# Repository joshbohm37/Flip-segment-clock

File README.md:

# Flip Segment Clock
A desktop clock centered around electromechanical 7 segment flip displays.

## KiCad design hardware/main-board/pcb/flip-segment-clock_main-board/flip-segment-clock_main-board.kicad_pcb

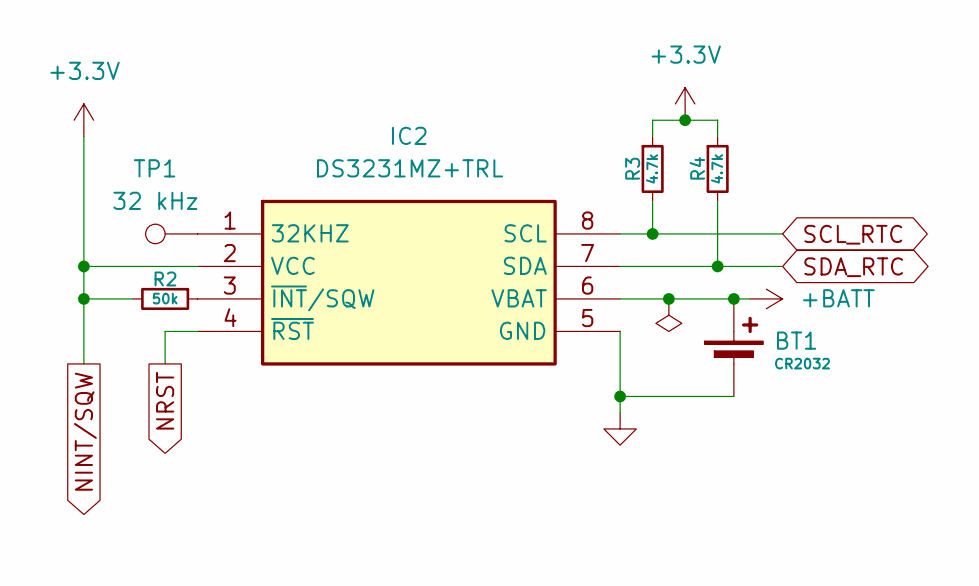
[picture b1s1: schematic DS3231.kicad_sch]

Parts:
BT1: CR2032; BatteryHolder_Keystone_1057_1x2032
IC2: DS3231MZ+TRL; SOIC127P600X175-8N; Mouser Part Number 700-DS3231MZ+TRL
R2: 50k; R_0402_1005Metric
R3, R4: 4.7k; R_0402_1005Metric
TP1: 32 kHz; TestPoint_Pad_D2.5mm

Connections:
+BATT: BT1.1 (+), IC2.6 (VBAT); also elsewhere on the board
GND: BT1.2 (-), IC2.5 (GND); also elsewhere on the board
NINT/SQW: IC2.2 (VCC), R2.2, R3.1, R4.1; also elsewhere on the board
NRST: IC2.4 (~RST)
unnamed: IC2.1 (32KHZ), TP1.1
unnamed: IC2.3 (~INT/SQW), R2.1
SCL_RTC: IC2.8 (SCL), R3.2
SDA_RTC: IC2.7 (SDA), R4.2

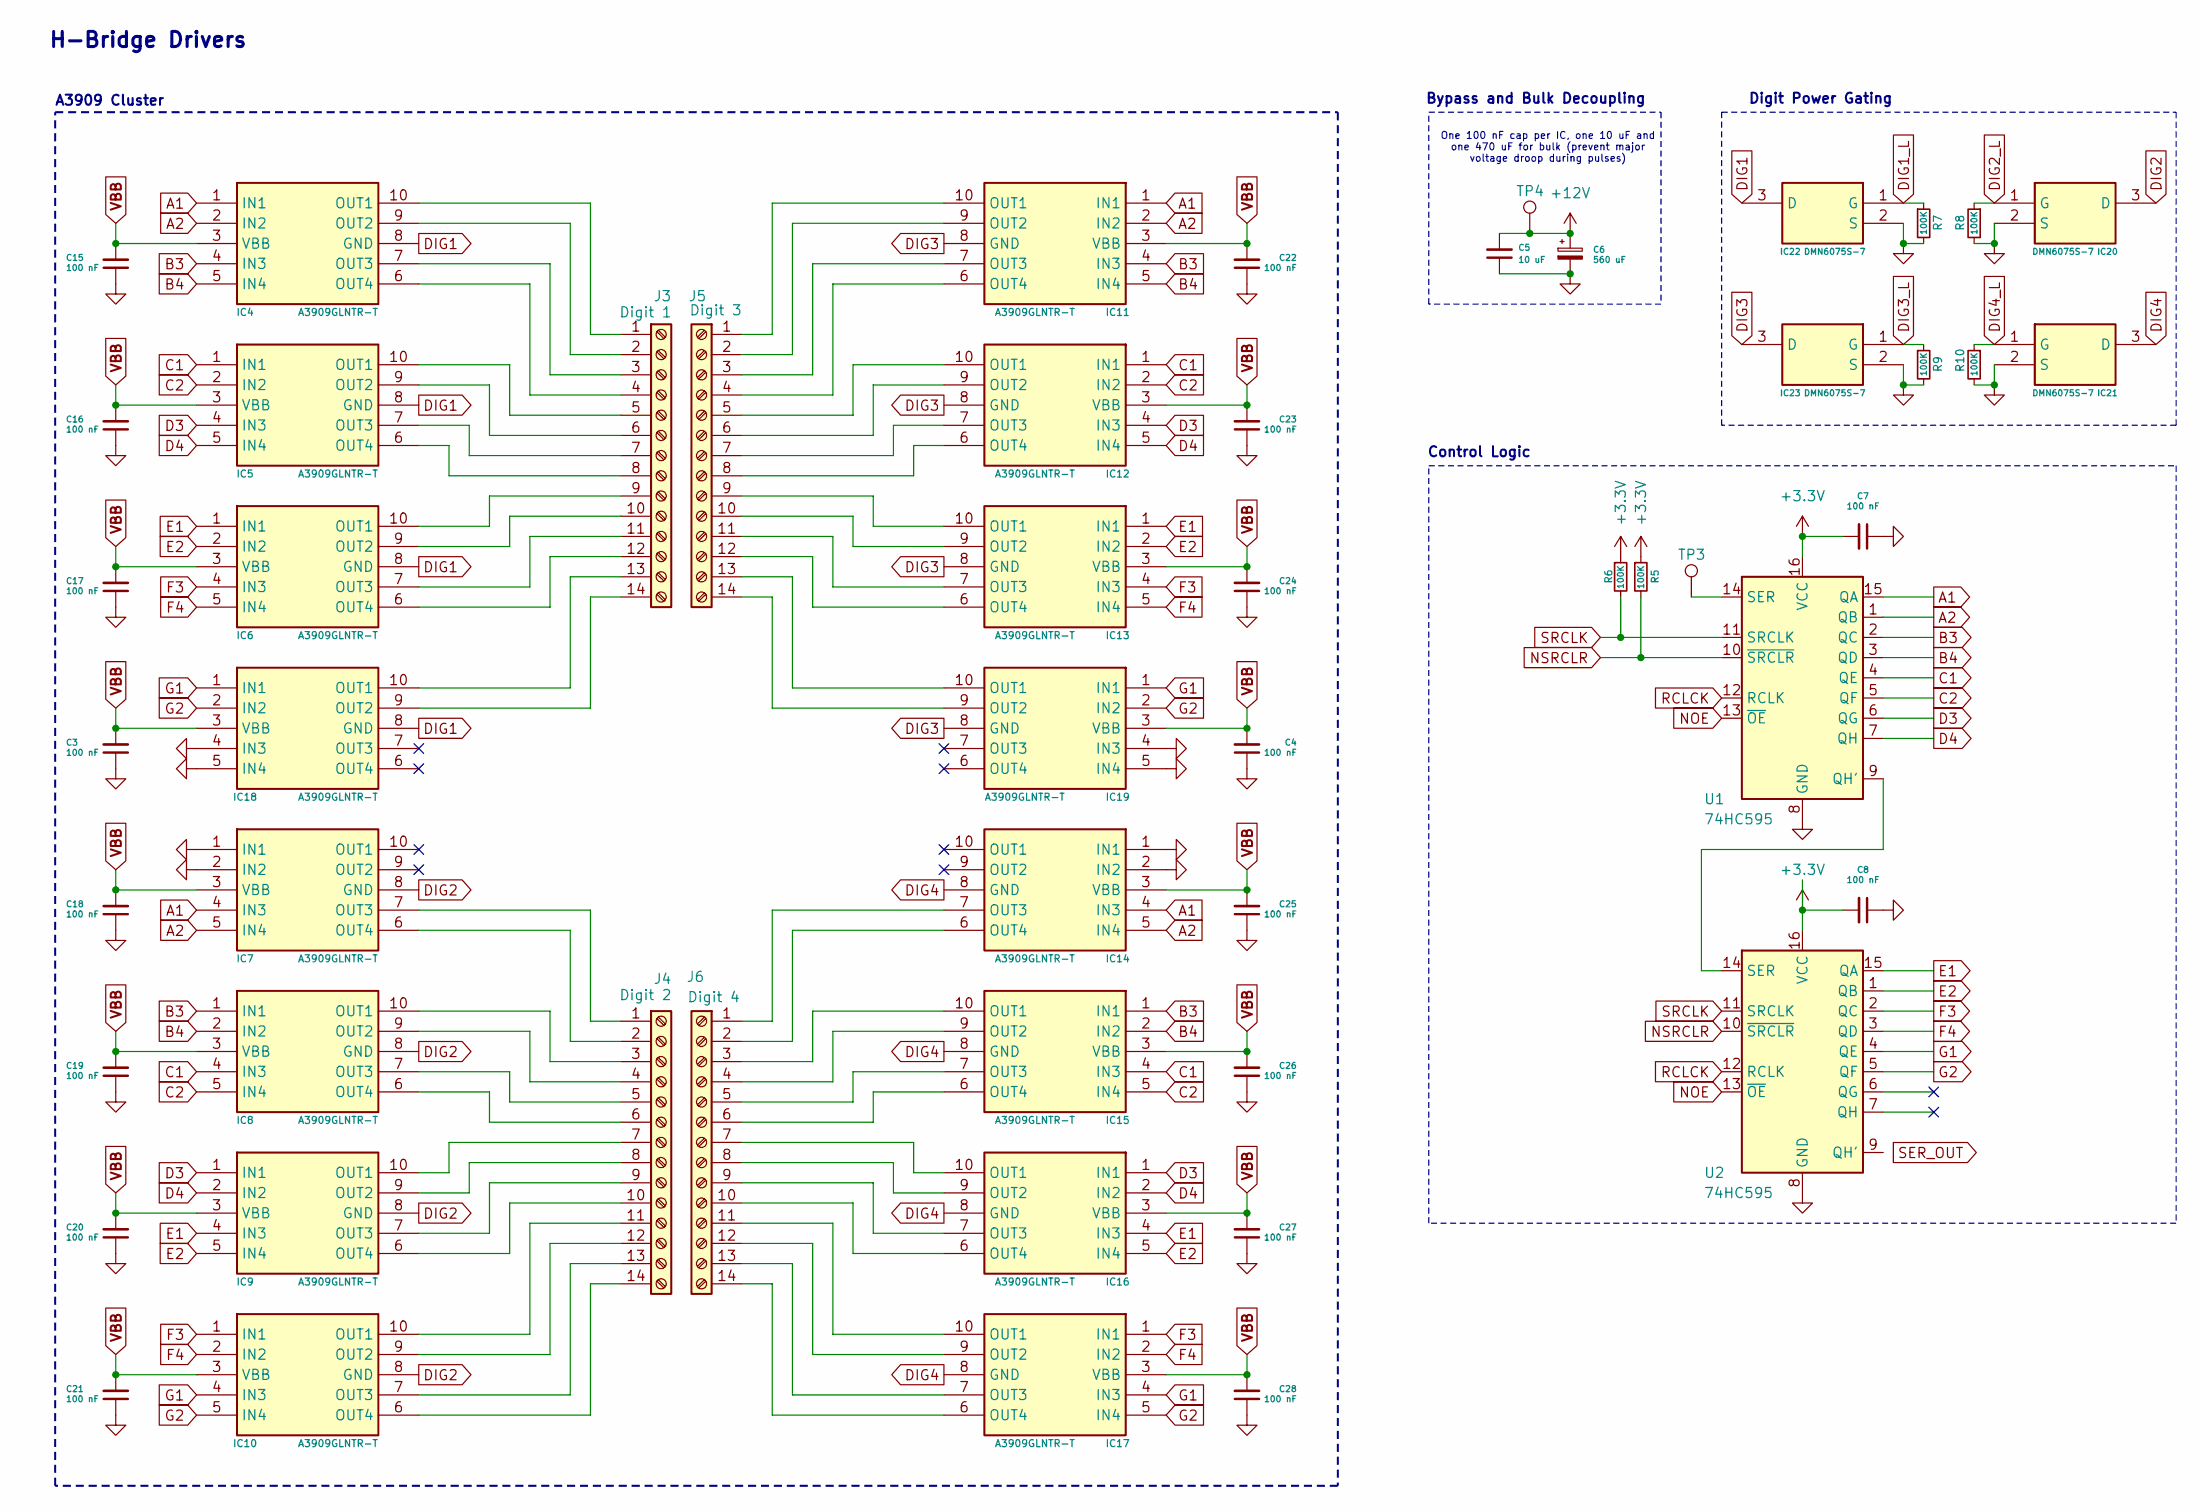
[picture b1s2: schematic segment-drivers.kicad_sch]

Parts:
C3, C4, C7, C8, C15, C16, C17, C18, C19, C20, C21, C22, C23, C24, C25, C26, C27, C28: 100 nF; C_0402_1005Metric; Manufacturer part # CL05B104KA5NNNC; LCSC C155422
C5: 10 uF; C_1206_3216Metric; Manufacturer part # CL31A106KAHNNNE; LCSC C9807
C6: 560 uF; C_Elec_10x10.2; Manufacturer part # EMZR350ARA561MJA0G; LCSC C2163314
IC4, IC5, IC6, IC7, IC8, IC9, IC10, IC11, IC12, IC13, IC14, IC15, IC16, IC17, IC18, IC19: A3909GLNTR-T; SOP100P600X175-10N; Mouser Part Number 250-A3909GLNTR-T
IC20, IC21, IC22, IC23: DMN6075S-7; SOT96P240X110-3N; Mouser Part Number 621-DMN6075S-7
J3: Digit 1; TerminalBlock_Xinya_XY308-2.54-14P_1x14_P2.54mm_Horizontal
J4: Digit 2; TerminalBlock_Xinya_XY308-2.54-14P_1x14_P2.54mm_Horizontal
J5: Digit 3; TerminalBlock_Xinya_XY308-2.54-14P_1x14_P2.54mm_Horizontal
J6: Digit 4; TerminalBlock_Xinya_XY308-2.54-14P_1x14_P2.54mm_Horizontal
R5, R6: 100K; R_0402_1005Metric; Manufacturer part # 0402WGF1003TCE; LCSC C25741
R7, R8, R9, R10: 100K; R_0402_1005Metric
TP3: SER; TestPoint_Pad_D1.5mm
TP4: 12v; TestPoint_Pad_D1.5mm
U1, U2: 74HC595; SOIC-16_3.9x9.9mm_P1.27mm; Manufacturer part # 74HC595D,118; LCSC C5947

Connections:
+12V: C5.2, C6.1, TP4.1; also elsewhere on the board
A1: IC4.1 (IN1), IC7.4 (IN3), IC11.1 (IN1), IC14.4 (IN3), U1.15 (QA)
A2: IC4.2 (IN2), IC7.5 (IN4), IC11.2 (IN2), IC14.5 (IN4), U1.1 (QB)
B3: IC4.4 (IN3), IC8.1 (IN1), IC11.4 (IN3), IC15.1 (IN1), U1.2 (QC)
B4: IC4.5 (IN4), IC8.2 (IN2), IC11.5 (IN4), IC15.2 (IN2), U1.3 (QD)
C1: IC5.1 (IN1), IC8.4 (IN3), IC12.1 (IN1), IC15.4 (IN3), U1.4 (QE)
C2: IC5.2 (IN2), IC8.5 (IN4), IC12.2 (IN2), IC15.5 (IN4), U1.5 (QF)
D3: IC5.4 (IN3), IC9.1 (IN1), IC12.4 (IN3), IC16.1 (IN1), U1.6 (QG)
D4: IC5.5 (IN4), IC9.2 (IN2), IC12.5 (IN4), IC16.2 (IN2), U1.7 (QH)
DIG1: IC4.8 (GND), IC5.8 (GND), IC6.8 (GND), IC18.8 (GND), IC22.3 (D)
DIG1_L: IC22.1 (G), R7.1
DIG2: IC7.8 (GND), IC8.8 (GND), IC9.8 (GND), IC10.8 (GND), IC20.3 (D)
DIG2_L: IC20.1 (G), R8.1
DIG3: IC11.8 (GND), IC12.8 (GND), IC13.8 (GND), IC19.8 (GND), IC23.3 (D)
DIG3_L: IC23.1 (G), R9.1
DIG4: IC14.8 (GND), IC15.8 (GND), IC16.8 (GND), IC17.8 (GND), IC21.3 (D)
DIG4_L: IC21.1 (G), R10.1
E1: IC6.1 (IN1), IC9.4 (IN3), IC13.1 (IN1), IC16.4 (IN3), U2.15 (QA)
E2: IC6.2 (IN2), IC9.5 (IN4), IC13.2 (IN2), IC16.5 (IN4), U2.1 (QB)
F3: IC6.4 (IN3), IC10.1 (IN1), IC13.4 (IN3), IC17.1 (IN1), U2.2 (QC)
F4: IC6.5 (IN4), IC10.2 (IN2), IC13.5 (IN4), IC17.2 (IN2), U2.3 (QD)
G1: IC10.4 (IN3), IC17.4 (IN3), IC18.1 (IN1), IC19.1 (IN1), U2.4 (QE)
G2: IC10.5 (IN4), IC17.5 (IN4), IC18.2 (IN2), IC19.2 (IN2), U2.5 (QF)
GND: C3.1, C4.1, C5.1, C6.2, C7.1, C8.1, C15.1, C16.1, C17.1, C18.1, C19.1, C20.1, C21.1, C22.1, C23.1, C24.1, C25.1, C26.1, C27.1, C28.1, IC7.1 (IN1), IC7.2 (IN2), IC14.1 (IN1), IC14.2 (IN2), IC18.4 (IN3), IC18.5 (IN4), IC19.4 (IN3), IC19.5 (IN4), IC20.2 (S), IC21.2 (S), IC22.2 (S), IC23.2 (S), R7.2, R8.2, R9.2, R10.2, U1.8 (GND), U2.8 (GND); also elsewhere on the board
NINT/SQW: C7.2, C8.2, R5.1, R6.1, U1.16 (VCC), U2.16 (VCC); also elsewhere on the board
NOE: U1.13 (~OE), U2.13 (~OE)
NSRCLR: R5.2, U1.10 (~SRCLR), U2.10 (~SRCLR)
unnamed: IC4.10 (OUT1), J3.1
unnamed: IC4.9 (OUT2), J3.2
unnamed: IC4.7 (OUT3), J3.3
unnamed: IC4.6 (OUT4), J3.4
unnamed: IC5.10 (OUT1), J3.5
unnamed: IC5.9 (OUT2), J3.6
unnamed: IC5.7 (OUT3), J3.7
unnamed: IC5.6 (OUT4), J3.8
unnamed: IC6.10 (OUT1), J3.9
unnamed: IC6.9 (OUT2), J3.10
unnamed: IC6.7 (OUT3), J3.11
unnamed: IC6.6 (OUT4), J3.12
unnamed: IC7.7 (OUT3), J4.1
unnamed: IC7.6 (OUT4), J4.2
unnamed: IC8.10 (OUT1), J4.3
unnamed: IC8.9 (OUT2), J4.4
unnamed: IC8.7 (OUT3), J4.5
unnamed: IC8.6 (OUT4), J4.6
unnamed: IC9.10 (OUT1), J4.7
unnamed: IC9.9 (OUT2), J4.8
unnamed: IC9.7 (OUT3), J4.9
unnamed: IC9.6 (OUT4), J4.10
unnamed: IC10.10 (OUT1), J4.11
unnamed: IC10.9 (OUT2), J4.12
unnamed: IC10.7 (OUT3), J4.13
unnamed: IC10.6 (OUT4), J4.14
unnamed: IC11.10 (OUT1), J5.1
unnamed: IC11.9 (OUT2), J5.2
unnamed: IC11.7 (OUT3), J5.3
unnamed: IC11.6 (OUT4), J5.4
unnamed: IC12.10 (OUT1), J5.5
unnamed: IC12.9 (OUT2), J5.6
unnamed: IC12.7 (OUT3), J5.7
unnamed: IC12.6 (OUT4), J5.8
unnamed: IC13.10 (OUT1), J5.9
unnamed: IC13.9 (OUT2), J5.10
unnamed: IC13.7 (OUT3), J5.11
unnamed: IC13.6 (OUT4), J5.12
unnamed: IC14.7 (OUT3), J6.1
unnamed: IC14.6 (OUT4), J6.2
unnamed: IC15.10 (OUT1), J6.3
unnamed: IC15.9 (OUT2), J6.4
unnamed: IC15.7 (OUT3), J6.5
unnamed: IC15.6 (OUT4), J6.6
unnamed: IC16.10 (OUT1), J6.7
unnamed: IC16.9 (OUT2), J6.8
unnamed: IC16.7 (OUT3), J6.9
unnamed: IC16.6 (OUT4), J6.10
unnamed: IC17.10 (OUT1), J6.11
unnamed: IC17.9 (OUT2), J6.12
unnamed: IC17.7 (OUT3), J6.13
unnamed: IC17.6 (OUT4), J6.14
unnamed: IC18.10 (OUT1), J3.13
unnamed: IC18.9 (OUT2), J3.14
unnamed: IC19.10 (OUT1), J5.13
unnamed: IC19.9 (OUT2), J5.14
unnamed: U1.9 (QH'), U2.14 (SER)
unnamed: TP3.1, U1.14 (SER)
RCLCK: U1.12 (RCLK), U2.12 (RCLK)
SRCLK: R6.2, U1.11 (SRCLK), U2.11 (SRCLK)
VBB: C3.2, C4.2, C15.2, C16.2, C17.2, C18.2, C19.2, C20.2, C21.2, C22.2, C23.2, C24.2, C25.2, C26.2, C27.2, C28.2, IC4.3 (VBB), IC5.3 (VBB), IC6.3 (VBB), IC7.3 (VBB), IC8.3 (VBB), IC9.3 (VBB), IC10.3 (VBB), IC11.3 (VBB), IC12.3 (VBB), IC13.3 (VBB), IC14.3 (VBB), IC15.3 (VBB), IC16.3 (VBB), IC17.3 (VBB), IC18.3 (VBB), IC19.3 (VBB)

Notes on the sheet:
Control Logic
H-Bridge Drivers
Digit Power Gating
Bypass and Bulk Decoupling
One 100 nF cap per IC, one 10 uF and one 470 uF for bulk (prevent major voltage droop during pulses)
A3909 Cluster

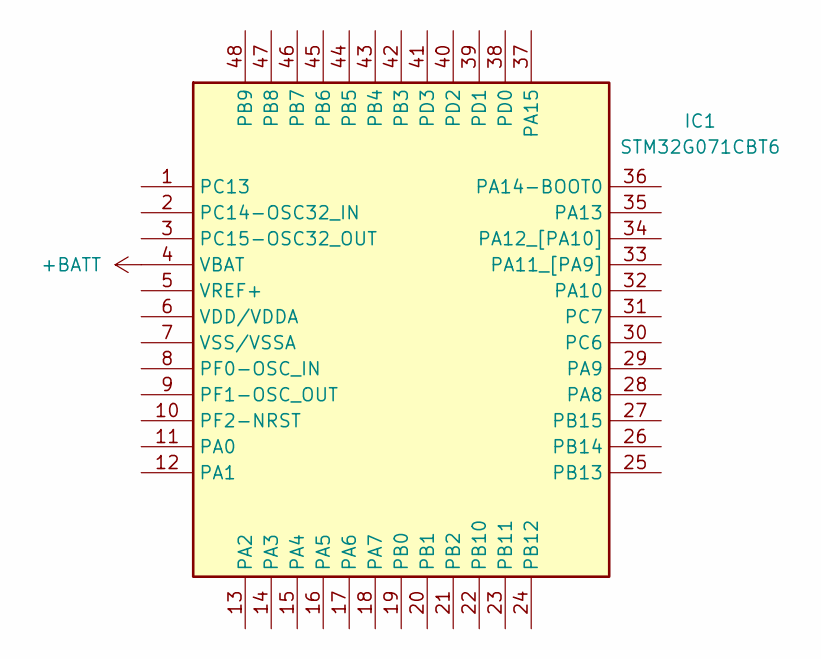
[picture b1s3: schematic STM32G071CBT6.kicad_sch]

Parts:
IC1: STM32G071CBT6; QFP50P900X900X160-48N; Mouser Part Number 511-STM32G071CBT6

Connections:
+BATT: IC1.4 (VBAT); also elsewhere on the board

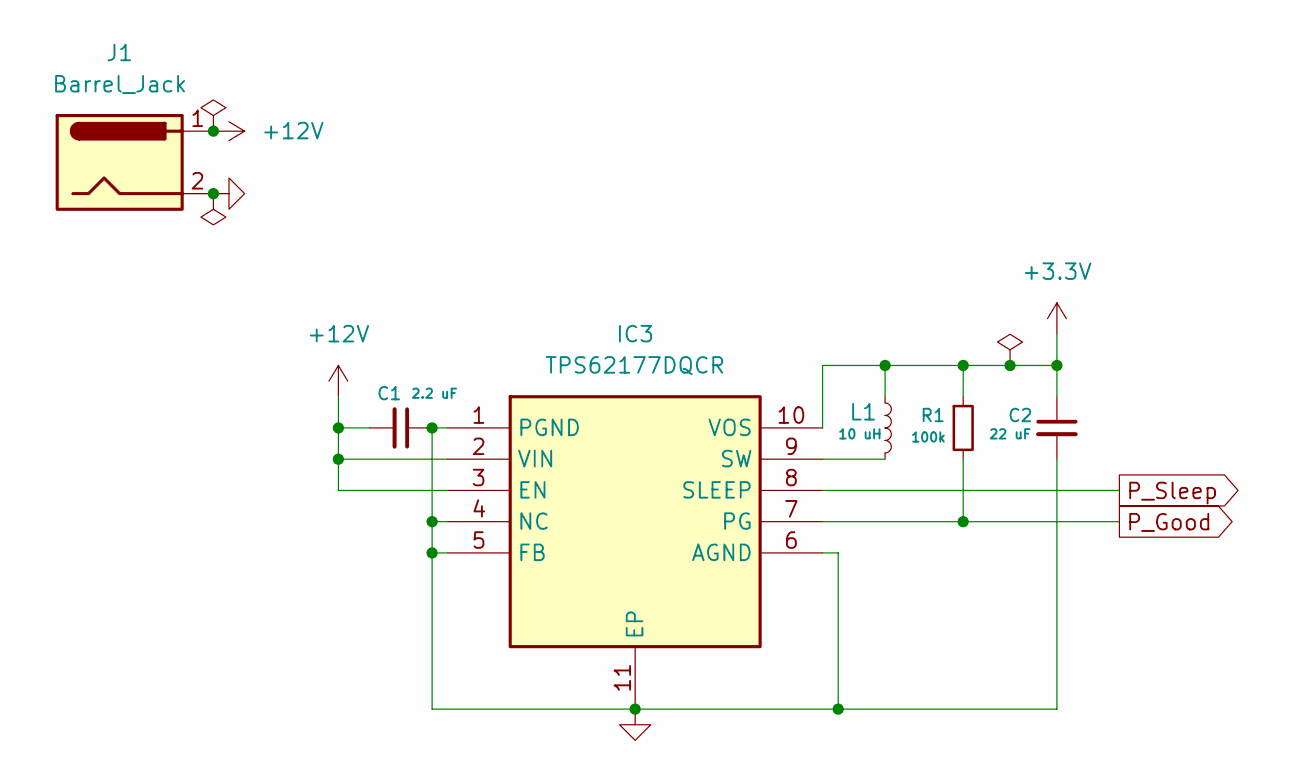
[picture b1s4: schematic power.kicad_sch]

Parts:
C1: 2.2 uF; C_0402_1005Metric
C2: 22 uF; C_0402_1005Metric
IC3: TPS62177DQCR; SON50P200X300X80-11N; Mouser Part Number 595-TPS62177DQCR
J1: Barrel_Jack; BarrelJack_SwitchcraftConxall_RAPC10U_Horizontal
L1: 10 uH; L_Coilcraft_LPS4018
R1: 100k; R_0402_1005Metric

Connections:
+12V: C1.2, IC3.2 (VIN), IC3.3 (EN), J1.1; also elsewhere on the board
GND: C1.1, C2.2, IC3.1 (PGND), IC3.4 (NC), IC3.5 (FB), IC3.6 (AGND), IC3.11 (EP), J1.2; also elsewhere on the board
NINT/SQW: C2.1, IC3.10 (VOS), L1.1, R1.1; also elsewhere on the board
unnamed: IC3.9 (SW), L1.2
P_Good: IC3.7 (PG), R1.2
P_Sleep: IC3.8 (SLEEP)

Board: 2 copper layers, 67 parts (0 on the bottom side), 95 nets, no tracks yet.

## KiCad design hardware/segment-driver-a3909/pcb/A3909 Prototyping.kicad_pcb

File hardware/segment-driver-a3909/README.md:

# a3909 segment driver breakout board
A breakout board used for driving 1 inch 7 segment electromechanical displays. Built around the A3909. Designed to test electrical properties/control mechanisms for the alfazeta 7 segment flip displays. Design will be integrated into final main board.

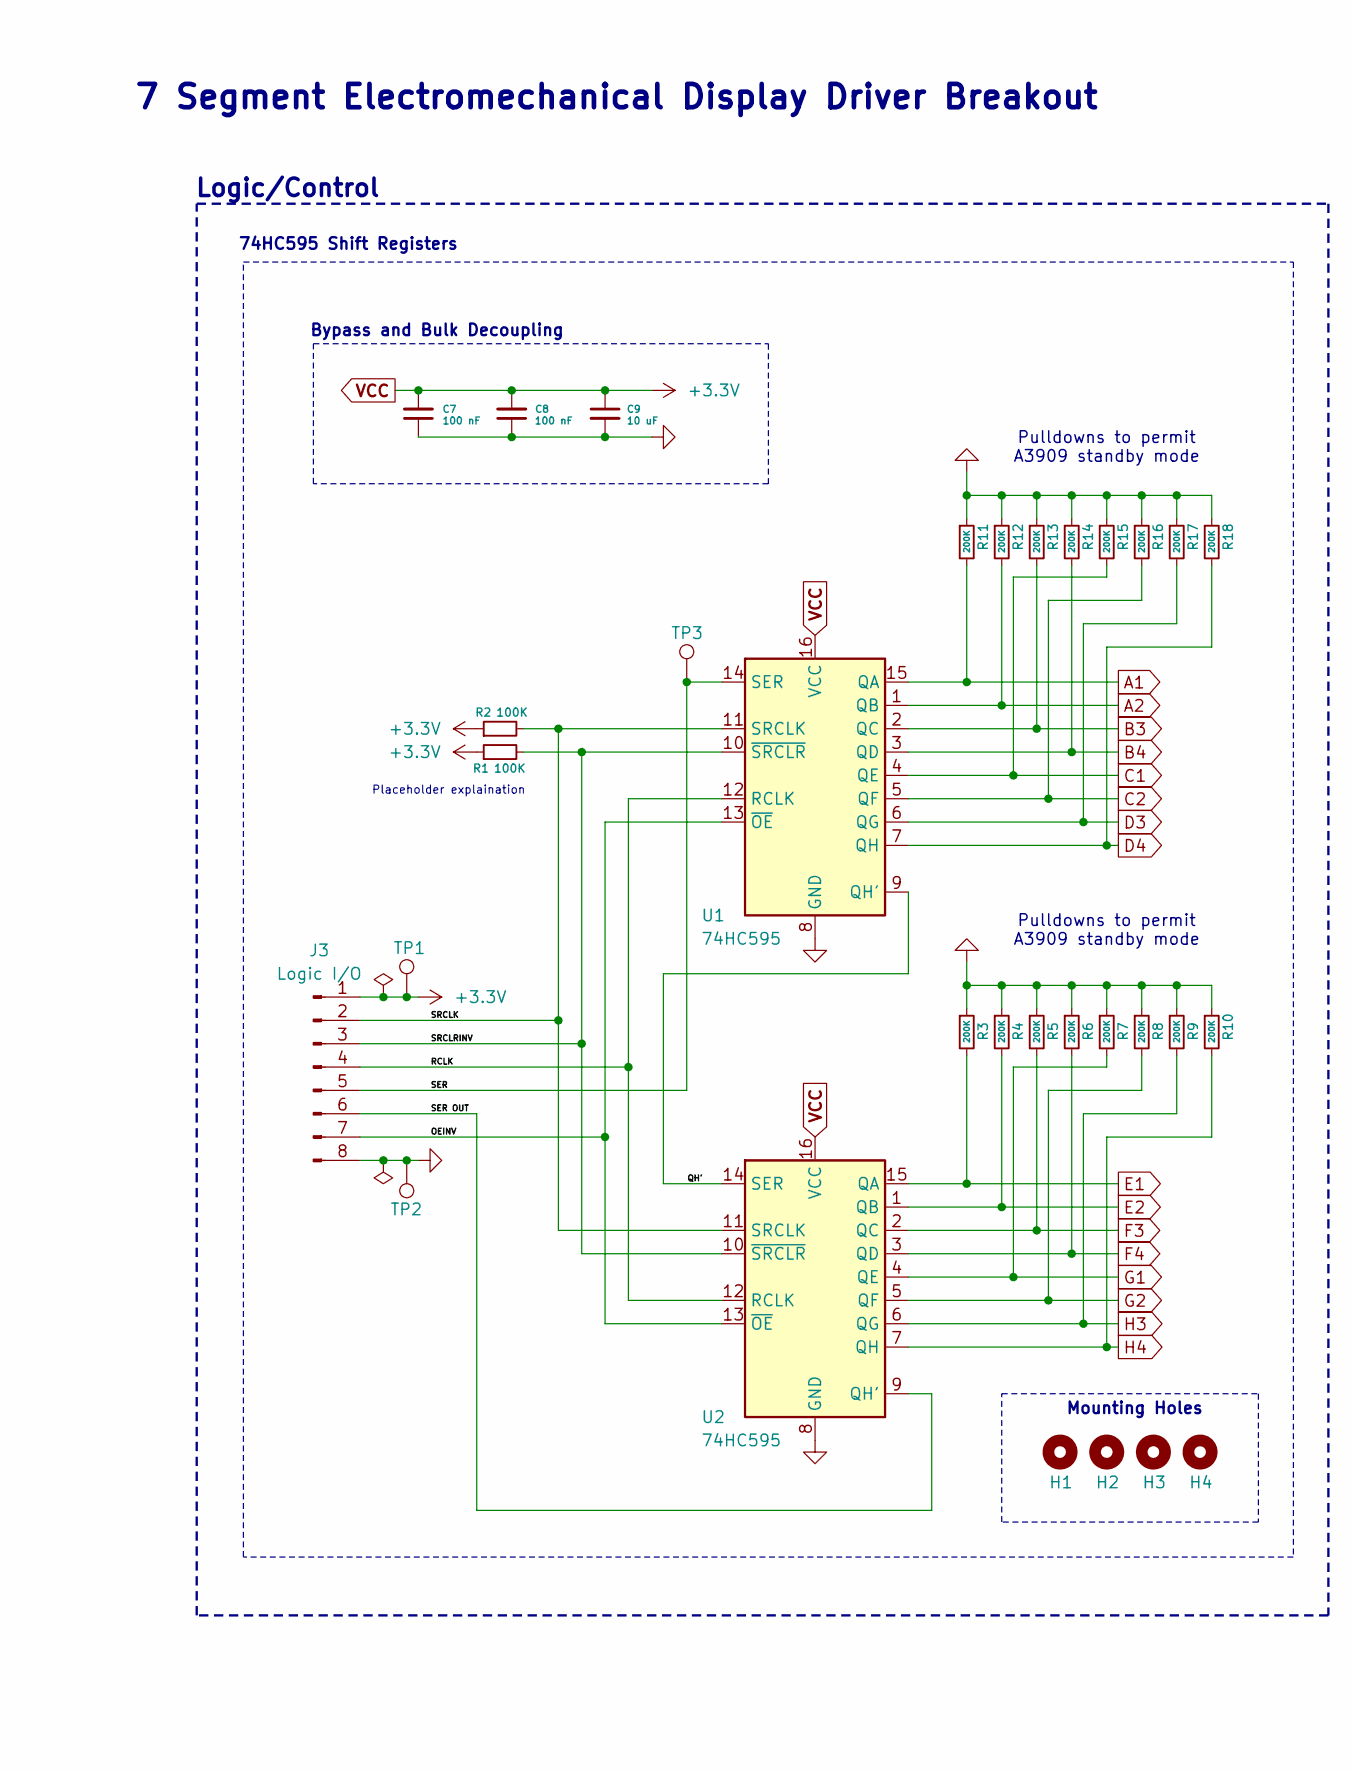
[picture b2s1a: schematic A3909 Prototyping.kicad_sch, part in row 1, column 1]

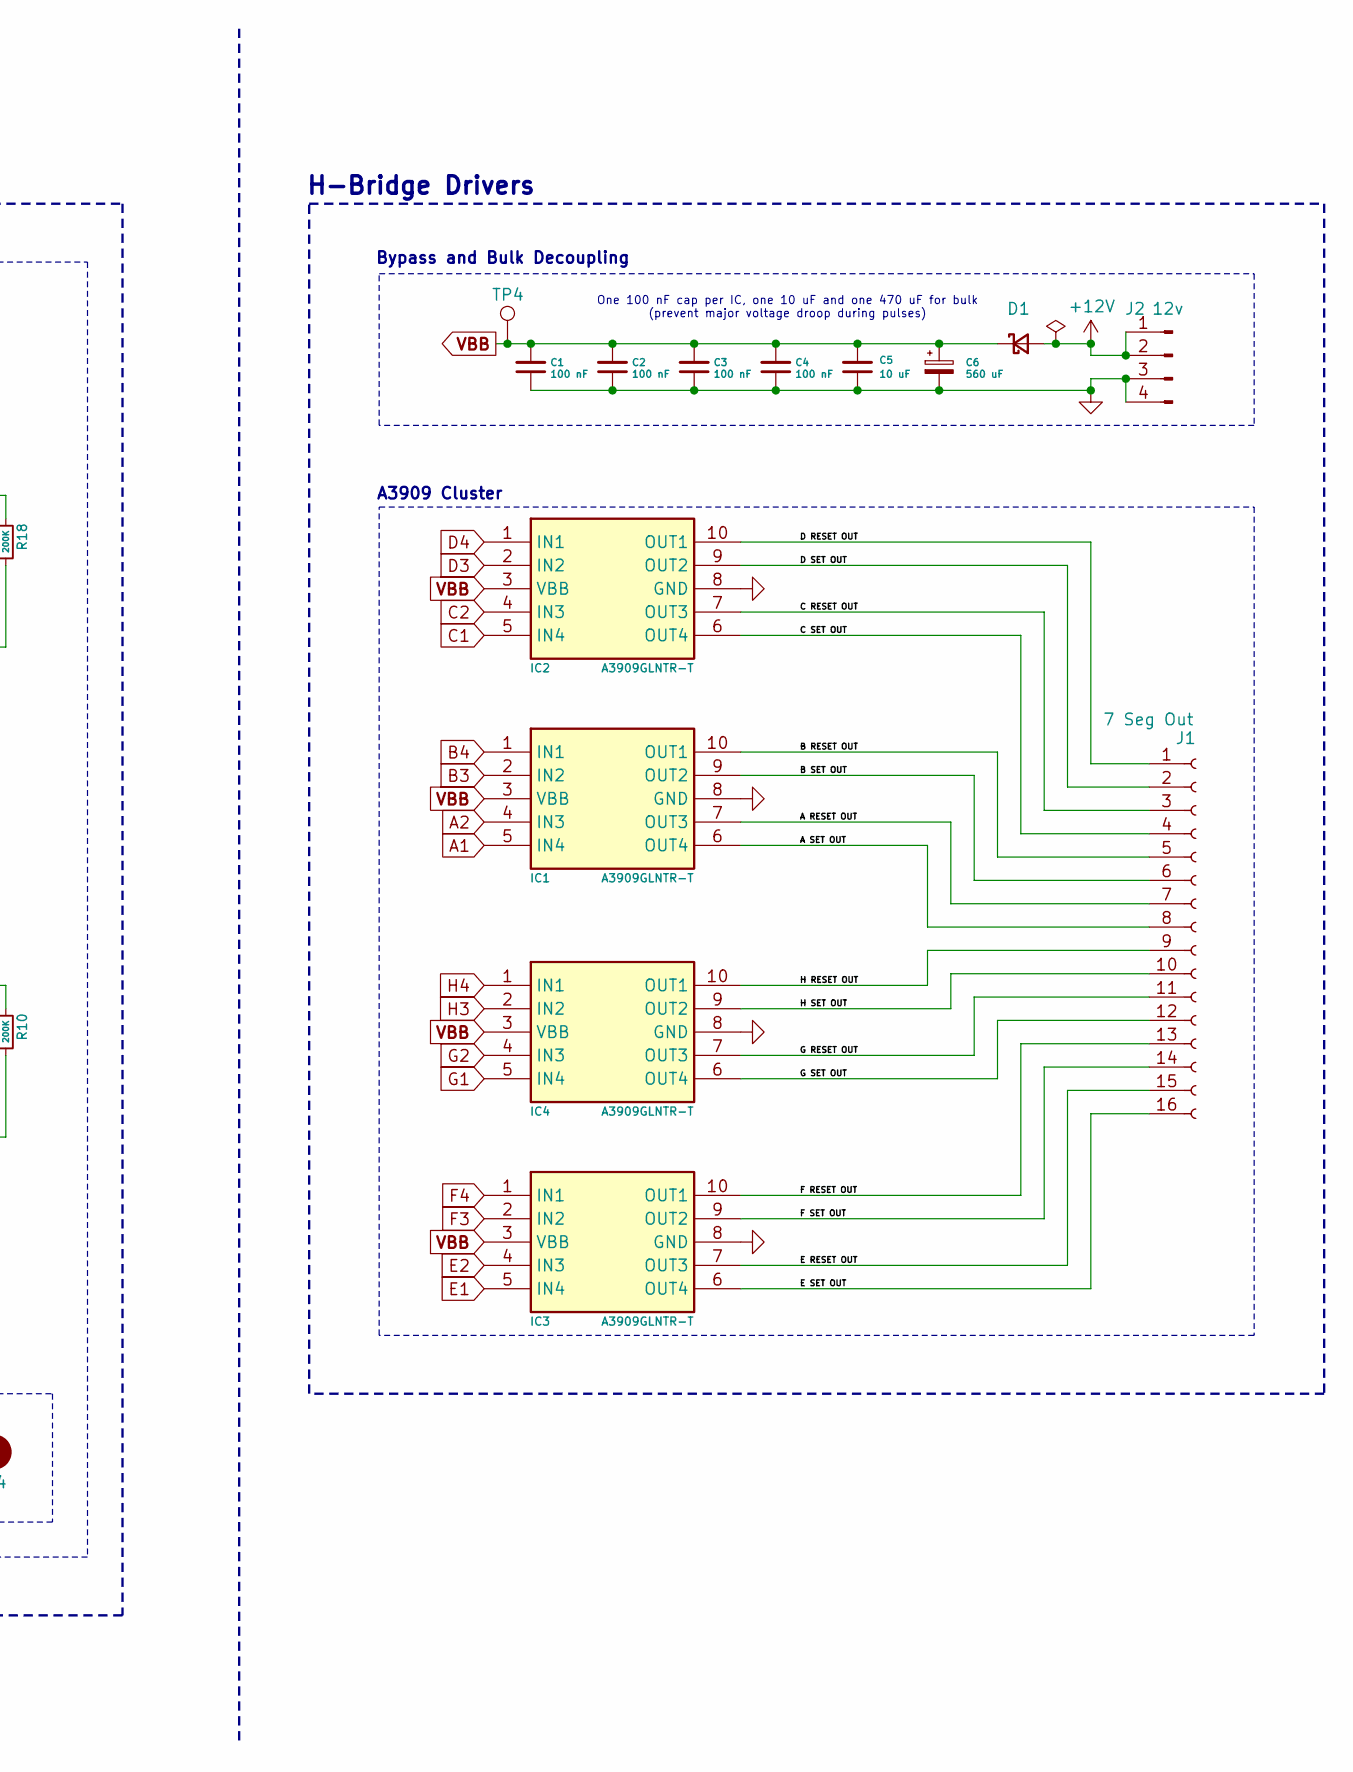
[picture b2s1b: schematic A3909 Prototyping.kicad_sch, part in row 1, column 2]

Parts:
C1, C2, C3, C4, C7, C8: 100 nF; C_0402_1005Metric; Manufacturer part # CL05B104KA5NNNC; LCSC C155422
C5, C9: 10 uF; C_1206_3216Metric; Manufacturer part # CL31A106KAHNNNE; LCSC C9807
C6: 560 uF; C_Elec_10x10.2; Manufacturer part # EMZR350ARA561MJA0G; LCSC C2163314
D1: D_Schottky_Small; D_SMB; Manufacturer part # SS54B; LCSC C32513
H1, H2, H3, H4: MountingHole; MountingHole_2.2mm_M2
IC1, IC2, IC3, IC4: A3909GLNTR-T; SOP100P600X175-10N; Mouser Part Number 250-A3909GLNTR-T
J1: 7 Seg Out; PinHeader_1x16_P2.54mm_Vertical; Manufacturer part # DS1021-1x16SF11-B; LCSC C7430372
J2: 12v; PinHeader_1x04_P2.54mm_Vertical; Manufacturer part # KH-2.54PH180-1X4P-L11.5; LCSC C2905435
J3: Logic I/O; PinHeader_1x08_P2.54mm_Vertical; Manufacturer part # KH-2.54PH180-1X8P-L11.5; LCSC C2905487
R1, R2: 100K; R_0402_1005Metric; Manufacturer part # 0402WGF1003TCE; LCSC C25741
R3, R4, R5, R6, R7, R8, R9, R10, R11, R12, R13, R14, R15, R16, R17, R18: 200K; R_0402_1005Metric; Manufacturer part # 0402WGF2003TCE; LCSC C25764
TP1: 3.3v; TestPoint_Pad_D1.5mm
TP2: GND; TestPoint_Pad_D1.5mm
TP3: SER; TestPoint_Pad_D1.5mm
TP4: 12v; TestPoint_Pad_D1.5mm
U1, U2: 74HC595; SOIC-16_3.9x9.9mm_P1.27mm; Manufacturer part # 74HC595D,118; LCSC C5947

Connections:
+12V: D1.2 (A), J2.1, J2.2
/A RESET OUT: IC1.7 (OUT3), J1.7
/A SET OUT: IC1.6 (OUT4), J1.8
/B RESET OUT: IC1.10 (OUT1), J1.5
/B SET OUT: IC1.9 (OUT2), J1.6
/C RESET OUT: IC2.7 (OUT3), J1.3
/C SET OUT: IC2.6 (OUT4), J1.4
/D RESET OUT: IC2.10 (OUT1), J1.1
/D SET OUT: IC2.9 (OUT2), J1.2
/E RESET OUT: IC3.7 (OUT3), J1.15
/E SET OUT: IC3.6 (OUT4), J1.16
/F RESET OUT: IC3.10 (OUT1), J1.13
/F SET OUT: IC3.9 (OUT2), J1.14
/G RESET OUT: IC4.7 (OUT3), J1.11
/G SET OUT: IC4.6 (OUT4), J1.12
/H RESET OUT: IC4.10 (OUT1), J1.9
/H SET OUT: IC4.9 (OUT2), J1.10
/OEINV: J3.7, U1.13 (~OE), U2.13 (~OE)
/QH': U1.9 (QH'), U2.14 (SER)
/RCLK: J3.4, U1.12 (RCLK), U2.12 (RCLK)
/SER: J3.5, TP3.1, U1.14 (SER)
/SER OUT: J3.6, U2.9 (QH')
/SRCLK: J3.2, R2.2, U1.11 (SRCLK), U2.11 (SRCLK)
/SRCLRINV: J3.3, R1.2, U1.10 (~SRCLR), U2.10 (~SRCLR)
A1: IC1.5 (IN4), R11.2, U1.15 (QA)
A2: IC1.4 (IN3), R12.2, U1.1 (QB)
B3: IC1.2 (IN2), R13.2, U1.2 (QC)
B4: IC1.1 (IN1), R14.2, U1.3 (QD)
C1: IC2.5 (IN4), R15.2, U1.4 (QE)
C2: IC2.4 (IN3), R16.2, U1.5 (QF)
D3: IC2.2 (IN2), R17.2, U1.6 (QG)
D4: IC2.1 (IN1), R18.2, U1.7 (QH)
E1: IC3.5 (IN4), R3.2, U2.15 (QA)
E2: IC3.4 (IN3), R4.2, U2.1 (QB)
F3: IC3.2 (IN2), R5.2, U2.2 (QC)
F4: IC3.1 (IN1), R6.2, U2.3 (QD)
G1: IC4.5 (IN4), R7.2, U2.4 (QE)
G2: IC4.4 (IN3), R8.2, U2.5 (QF)
GND: C1.1, C2.1, C3.1, C4.1, C5.1, C6.2, C7.1, C8.1, C9.2, IC1.8 (GND), IC2.8 (GND), IC3.8 (GND), IC4.8 (GND), J2.3, J2.4, J3.8, R3.1, R4.1, R5.1, R6.1, R7.1, R8.1, R9.1, R10.1, R11.1, R12.1, R13.1, R14.1, R15.1, R16.1, R17.1, R18.1, TP2.1, U1.8 (GND), U2.8 (GND)
H3: IC4.2 (IN2), R9.2, U2.6 (QG)
H4: IC4.1 (IN1), R10.2, U2.7 (QH)
VBB: C1.2, C2.2, C3.2, C4.2, C5.2, C6.1, D1.1 (K), IC1.3 (VBB), IC2.3 (VBB), IC3.3 (VBB), IC4.3 (VBB), TP4.1
VCC: C7.2, C8.2, C9.1, J3.1, R1.1, R2.1, TP1.1, U1.16 (VCC), U2.16 (VCC)

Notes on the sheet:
Pulldowns to permit A3909 standby mode
74HC595 Shift Registers
A3909 Cluster
7 Segment Electromechanical Display Driver Breakout
Placeholder explaination
Bypass and Bulk Decoupling
One 100 nF cap per IC, one 10 uF and one 470 uF for bulk (prevent major voltage droop during pulses)
Logic/Control
Mounting Holes
H-Bridge Drivers

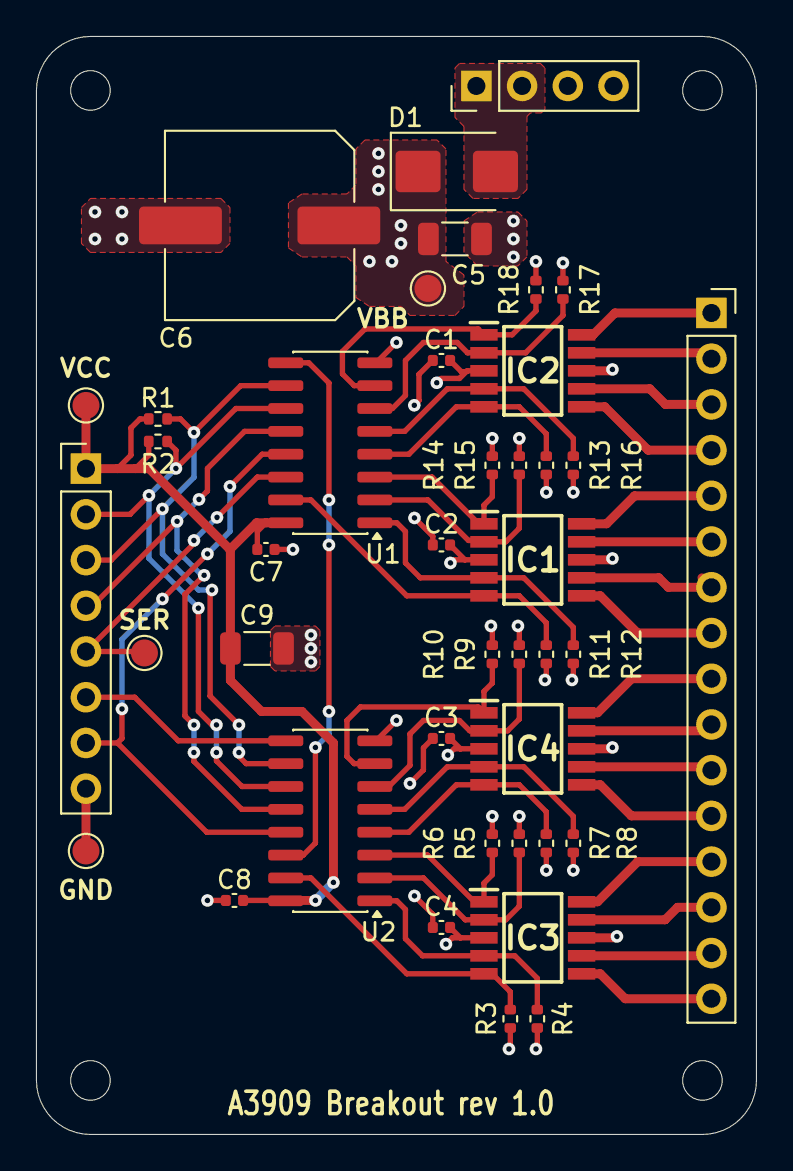
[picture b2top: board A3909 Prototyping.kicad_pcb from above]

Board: 2 copper layers, 40.0 x 61.0 mm, 45 parts (0 on the bottom side), 43 nets.

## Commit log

2025-11-30 Pullup/pulldowns Footprints
2025-12-03 Fin drivers, start voltage reg
2025-12-24 Restructuring of project
    Scope of this project exceeded the scope of the previous structure. Revamped the file structure to accommodate the entire flip segment clock project.
    -main folder now contains subfolders for each division of the project.
    -hardware folder now contains a subdirectory for each board that will be produced for the project.
    -created a docs folder to house github pages files.
2025-12-31 Documentation restructuring
    Added external documentation vs internal/design decision pages. setup github pages.
2025-12-31 Update index.md
    Create a main landing page for the pages website. Documentation of my documentation.
2025-12-31 Index.md styling updates
    Add jekyll theme, default.html to enable mermaid diagrams, slight wording tweaks.
2025-12-31 fix broken mermaid graph
2025-12-31 Documentation links
    Link to other documentation pages within the index.md documentation guide.
2025-12-31 Theming + mermaid changes
2025-12-31 rename header
2025-12-31 DRC file addition
2026-01-02 Refining design of the segment drivers
2026-01-03 Segment driver update
    Continuing refinement of segment driver design, settle on per digit vbb isolation, no overlapping between a3909
2026-01-03 Finalizing design of digit VBB isolation
2026-01-03 Changelog/design notes for Segment Drivers
2026-01-03 Formatting Pages
2026-01-03 Formatting update
2026-01-26 Unsure
    Unsure of previous changes due to time off. Currently edited the lessons learned page.
2026-01-27 CubeMX setup
    Started a new cubemx project for the stm32 on the main board. Mainly enabled/labeled connectivity.
